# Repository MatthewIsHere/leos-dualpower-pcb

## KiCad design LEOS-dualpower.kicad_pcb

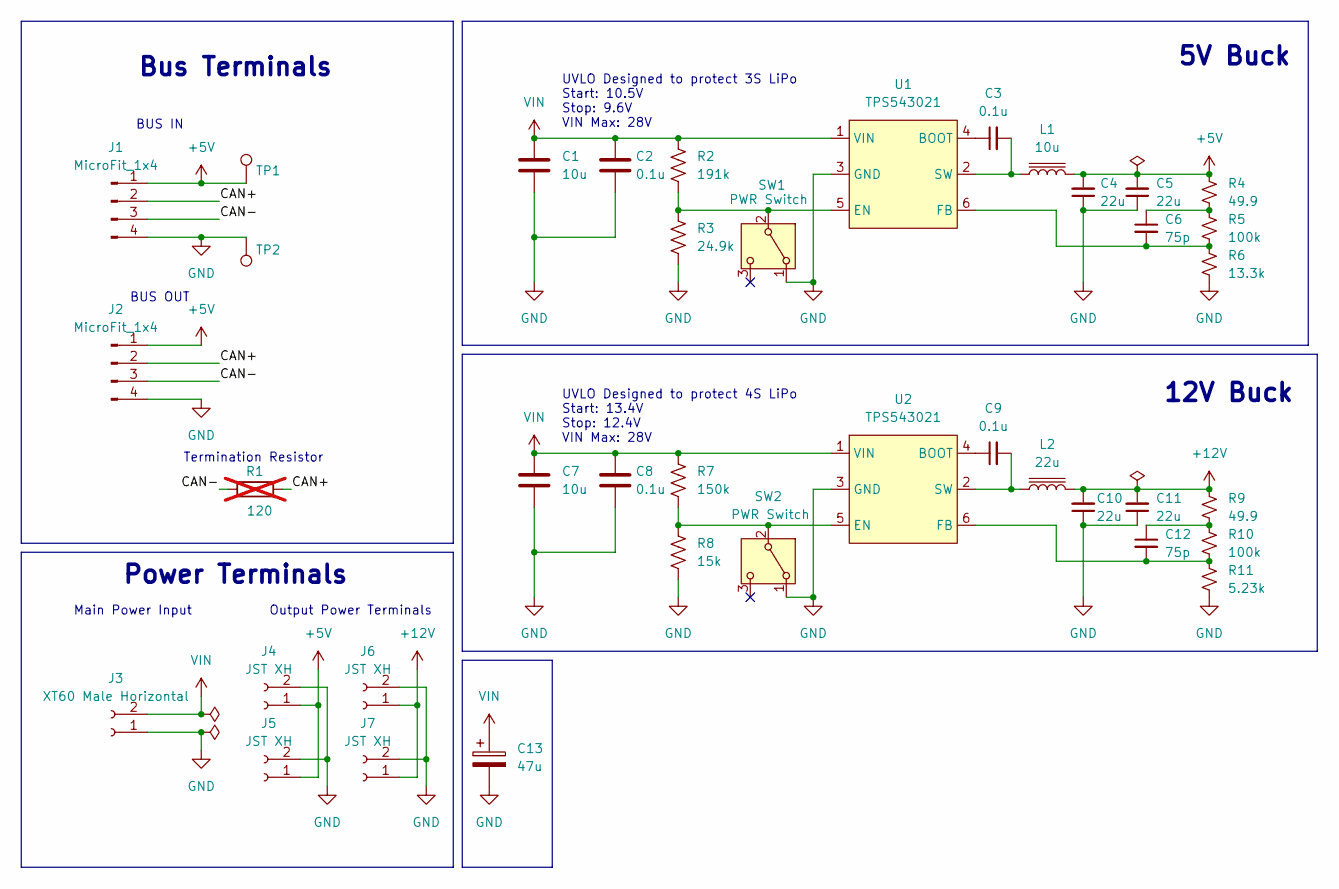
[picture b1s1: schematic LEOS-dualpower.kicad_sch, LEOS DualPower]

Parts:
C1, C7: 10u; C_1206_3216Metric_Pad1.33x1.80mm_HandSolder; MPN CL31B106KBHNNNE; Digikey 1276-6767-1-ND
C2, C3, C8, C9: 0.1u; C_1206_3216Metric_Pad1.33x1.80mm_HandSolder; MPN CL31B104KEHSFNE; Digikey 1276-3083-1-ND
C4, C5, C10, C11: 22u; C_1206_3216Metric_Pad1.33x1.80mm_HandSolder; MPN TMK316BBJ226ML-T; Digikey 587-3246-1-ND
C6, C12: 75p; C_1206_3216Metric_Pad1.33x1.80mm_HandSolder; MPN CC1206JRNPO9BN750; Digikey 13-CC1206JRNPO9BN750CT-ND
C13: 47u; C_Elec_6.3x7.7; MPN EDH476M050A9HAA; Digikey 399-18135-1-ND
J1, J2: MicroFit_1x4; Molex_MicroFit3.0_43650-0410_1x04_Horizontal; MPN 0436500409; Digikey WM1882CT-ND
J3: XT60 Male Horizontal; AMASS_XT60IPW-M_1x03_P7.20mm_Horizontal; MPN XT60IPW-M; Digikey amazon.com/dp/B0CQ2LM4JY
J4, J5, J6, J7: JST XH; JST_XH_S2B-XH-A_1x02_P2.50mm_Horizontal; MPN S2B-XH-A; Digikey 455-S2B-XH-A-ND
L1: 10u; L_Bourns_SRR1260; MPN SRR1280-100M; Digikey SRR1280-100MCT-ND
L2: 22u; L_Bourns_SRR1260; MPN SRR1280-220M; Digikey SRR1280-220MCT-ND
R1: 120; R_Axial_DIN0207_L6.3mm_D2.5mm_P7.62mm_Horizontal; MPN CF14JT120R; Digikey CF14JT120RCT-ND; not fitted
R2: 191k; R_1206_3216Metric_Pad1.30x1.75mm_HandSolder; MPN CRCW1206191KFKEA; Digikey 541-191KFCT-ND
R3: 24.9k; R_1206_3216Metric_Pad1.30x1.75mm_HandSolder; MPN CRCW120624K9FKEA; Digikey 541-24.9KFCT-ND
R4, R9: 49.9; R_1206_3216Metric_Pad1.30x1.75mm_HandSolder; MPN CRCW120649R9FKEAC; Digikey 541-4185-1-ND
R5, R10: 100k; R_1206_3216Metric_Pad1.30x1.75mm_HandSolder; MPN CRCW1206100KFKEAC; Digikey 541-4173-1-ND
R6: 13.3k; R_1206_3216Metric_Pad1.30x1.75mm_HandSolder; MPN CRCW120613K3FKEA; Digikey 541-13.3KFCT-ND
R7: 150k; R_1206_3216Metric_Pad1.30x1.75mm_HandSolder; MPN CRCW1206150KFKEAC; Digikey 541-CRCW1206150KFKEACCT-ND
R8: 15k; R_1206_3216Metric_Pad1.30x1.75mm_HandSolder; MPN CRCW120615K0FKEAC; Digikey 541-CRCW120615K0FKEACCT-ND
R11: 5.23k; R_1206_3216Metric_Pad1.30x1.75mm_HandSolder; MPN CRCW12065K23FKEA; Digikey 541-5.23KFCT-ND
SW1, SW2: PWR Switch; SW_Slide_SPDT_Angled_CK_OS102011MA1Q; MPN OS102011MA1QN1; Digikey CKN9559-ND
TP1: 5V Test Point; TestPoint_Loop_D2.60mm_Drill0.9mm_Beaded; MPN 5000; Digikey 36-5000-ND
TP2: GND Test Point; TestPoint_Loop_D2.60mm_Drill0.9mm_Beaded; MPN 5001; Digikey 36-5001-ND
U1, U2: TPS543021; SOT-563; MPN TPS543021DRLR; Digikey 296-TPS543021DRLRCT-ND

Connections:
+5V: C4.2, C5.2, J1.1, J2.1, J4.1, J5.1, L1.2, R4.1, TP1.1
+12V: C10.2, C11.2, J6.1, J7.1, L2.2, R9.1
/CAN+: J1.2, J2.2, R1.2
/CAN-: J1.3, J2.3, R1.1
GND: C1.2, C2.2, C4.1, C5.1, C7.2, C8.2, C10.1, C11.1, C13.2, J1.4, J2.4, J3.1, J4.2, J5.2, J6.2, J7.2, R3.2, R6.2, R8.2, R11.2, SW1.1 (A), SW2.1 (A), TP2.1, U1.3 (GND), U2.3 (GND)
unnamed: C6.1, R4.2, R5.1
unnamed: C12.1, R9.2, R10.1
unnamed: R2.2, R3.1, SW1.2 (B), U1.5 (EN)
unnamed: R7.2, R8.1, SW2.2 (B), U2.5 (EN)
unnamed: C3.1, U1.4 (BOOT)
unnamed: C6.2, R5.2, R6.1, U1.6 (FB)
unnamed: C3.2, L1.1, U1.2 (SW)
unnamed: C9.1, U2.4 (BOOT)
unnamed: C12.2, R10.2, R11.1, U2.6 (FB)
unnamed: C9.2, L2.1, U2.2 (SW)
VIN: C1.1, C2.1, C7.1, C8.1, C13.1, J3.2, R2.1, R7.1, U1.1 (VIN), U2.1 (VIN)

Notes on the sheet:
UVLO Designed to protect 3S LiPo Start: 10.5V Stop: 9.6V VIN Max: 28V
Output Power Terminals
Termination Resistor
Bus Terminals
12V Buck
BUS IN
UVLO Designed to protect 4S LiPo Start: 13.4V Stop: 12.4V VIN Max: 28V
Main Power Input
5V Buck
Power Terminals
BUS OUT

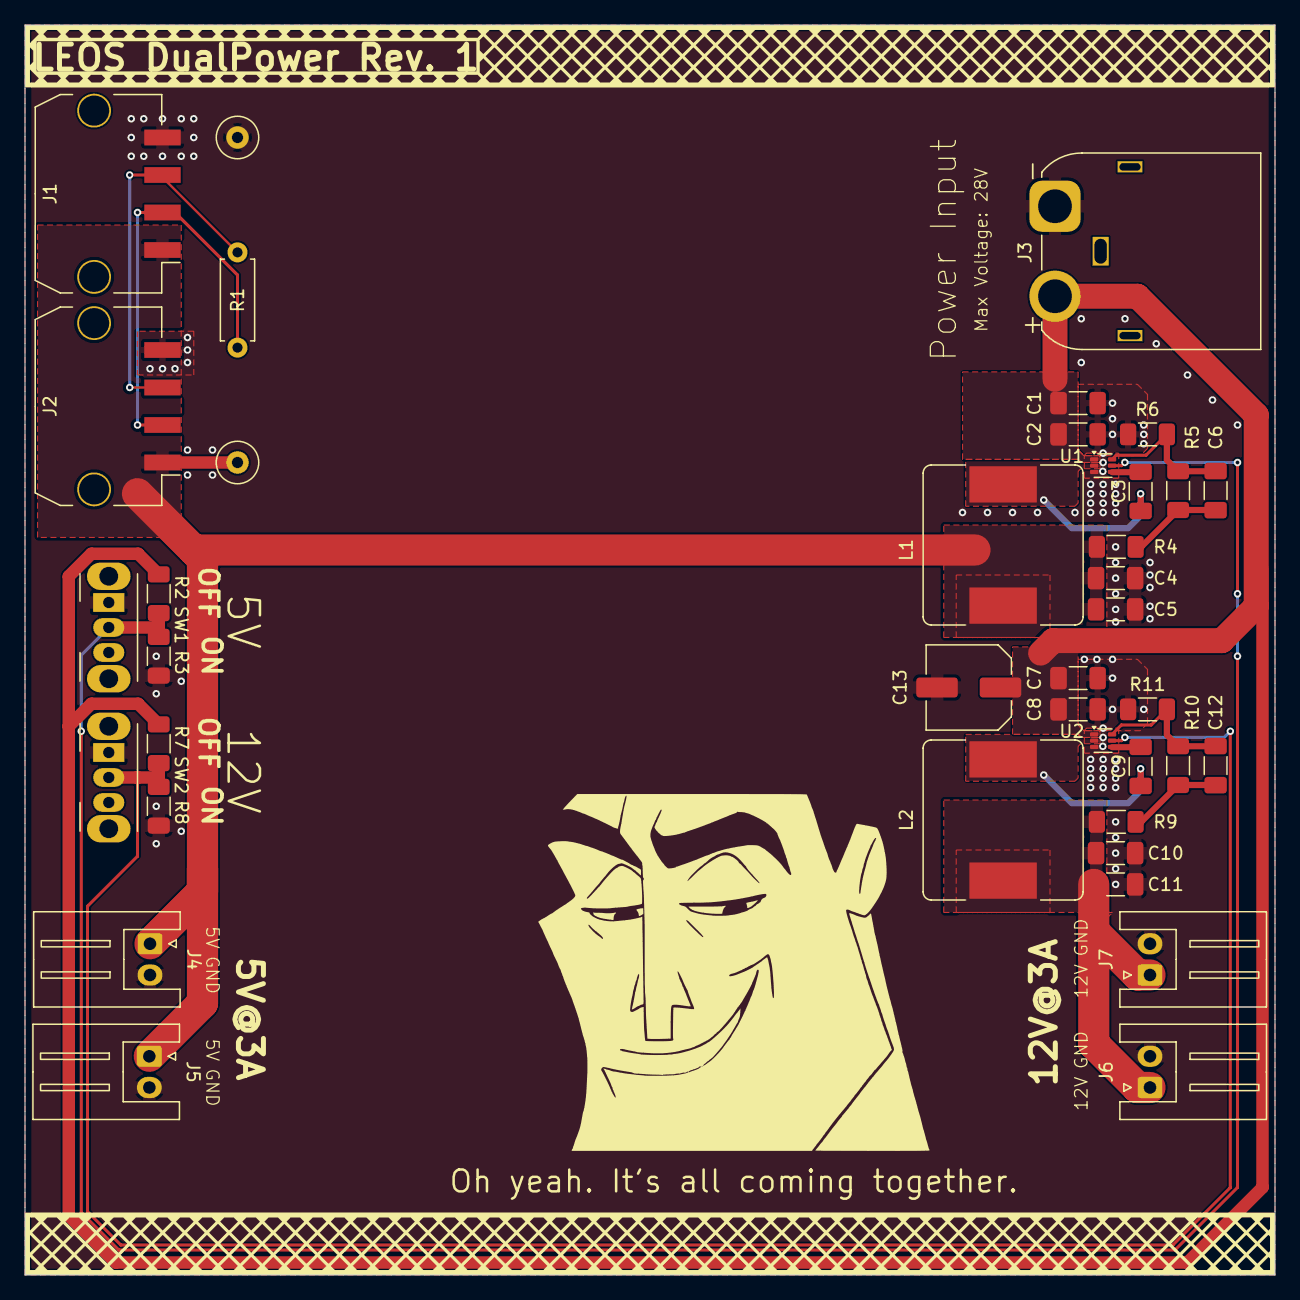
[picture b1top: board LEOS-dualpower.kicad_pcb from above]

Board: 2 copper layers, 100.0 x 100.0 mm, 39 parts (0 on the bottom side), 16 nets.

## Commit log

2026-03-20 create new pcb with dual 12V, 5V independent buck converters with simple components
2026-03-25 Fix output locations for generated files
